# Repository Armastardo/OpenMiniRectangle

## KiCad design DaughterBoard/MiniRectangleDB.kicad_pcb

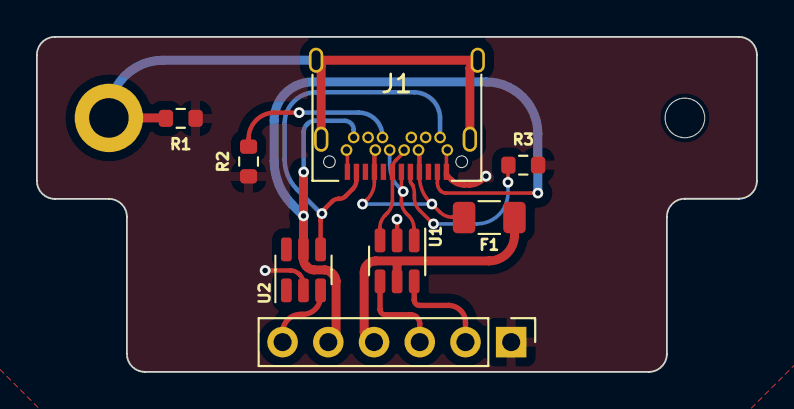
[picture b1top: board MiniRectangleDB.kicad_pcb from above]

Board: 2 copper layers, 40.0 x 18.6 mm, 10 parts (0 on the bottom side), 13 nets.

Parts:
F1: 500 mA; Fuse_1206_3216Metric
H1: MountingHole; MountingHole_2.2mm_M2
H2: MountingHole_Pad; MountingHole_2.2mm_M2_DIN965_Pad
J1: USB C Connector; TYPE-C_24P_QCHT
J2: Conn_01x06; PinHeader_1x06_P2.54mm_Vertical
R1: 1M; R_0603_1608Metric
R2, R3: 5.1k; R_0603_1608Metric
U1, U2: USBLC6-2SC6; SOT-23-6

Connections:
3vCable: J1.A2 (TX1+), J1.B2 (TX2+), J2.5, U2.5 (VBUS)
+5V: F1.2, J2.4, U1.5 (VBUS)
D+: J2.2, U1.6 (I/O1)
D-: J2.3, U1.4 (I/O2)
DATA: J2.6, U2.3 (I/O2)
DATABUS: J1.A11 (RX2+), J1.B11 (RX1+), U2.4 (I/O2)
DBUS+: J1.A6 (D+), J1.B6 (D+), U1.1 (I/O1)
DBUS-: J1.A7 (D-), J1.B7 (D-), U1.3 (I/O2)
GND: J1.A1 (GND), J1.A12 (GND), J1.B1 (GND), J1.B12 (GND), J2.1, R1.1, R2.1, R3.2, U1.2 (GND), U2.2 (GND)
unnamed: F1.1, J1.A4 (VBUS), J1.A9 (VBUS), J1.B4 (VBUS), J1.B9 (VBUS)
unnamed: J1.A5 (CC1), R3.1
unnamed: J1.B5 (CC2), R2.2
unnamed: H2.1, J1.S1 (SHIELD), R1.2

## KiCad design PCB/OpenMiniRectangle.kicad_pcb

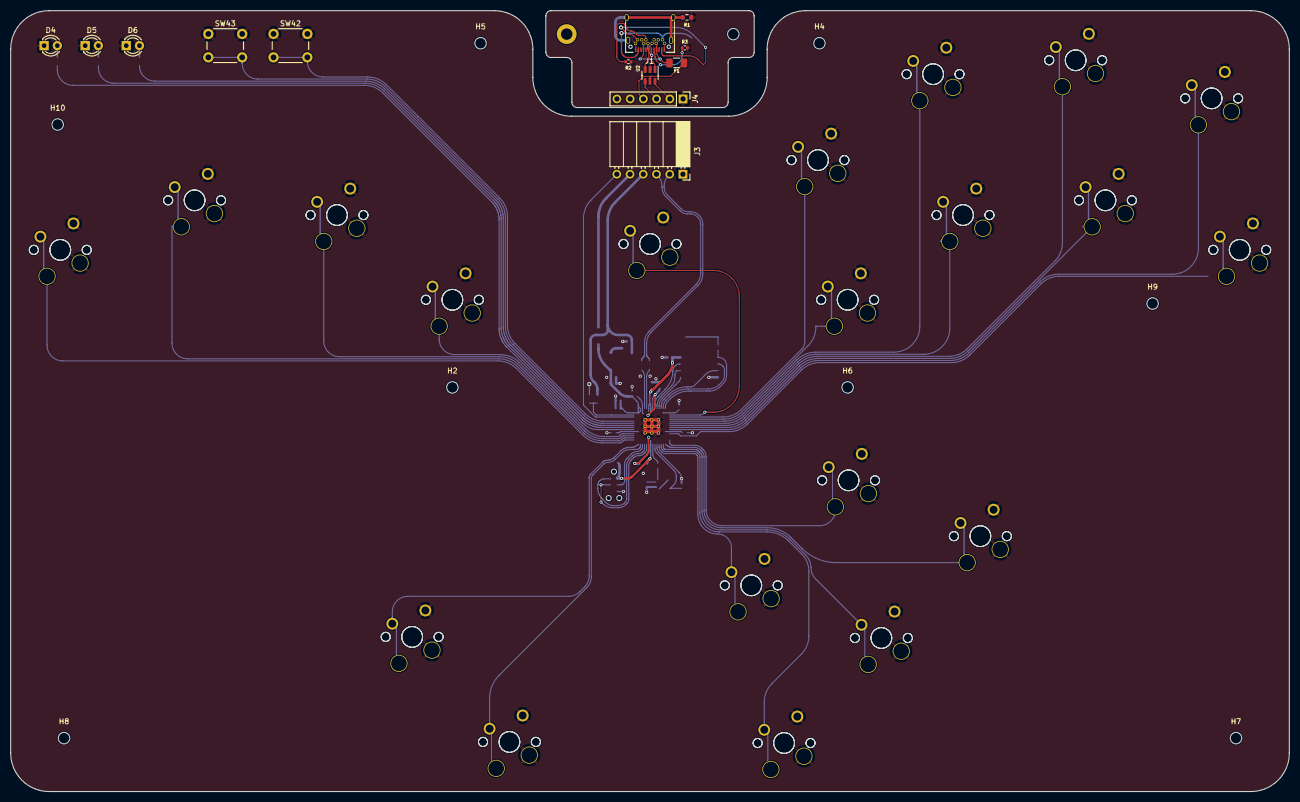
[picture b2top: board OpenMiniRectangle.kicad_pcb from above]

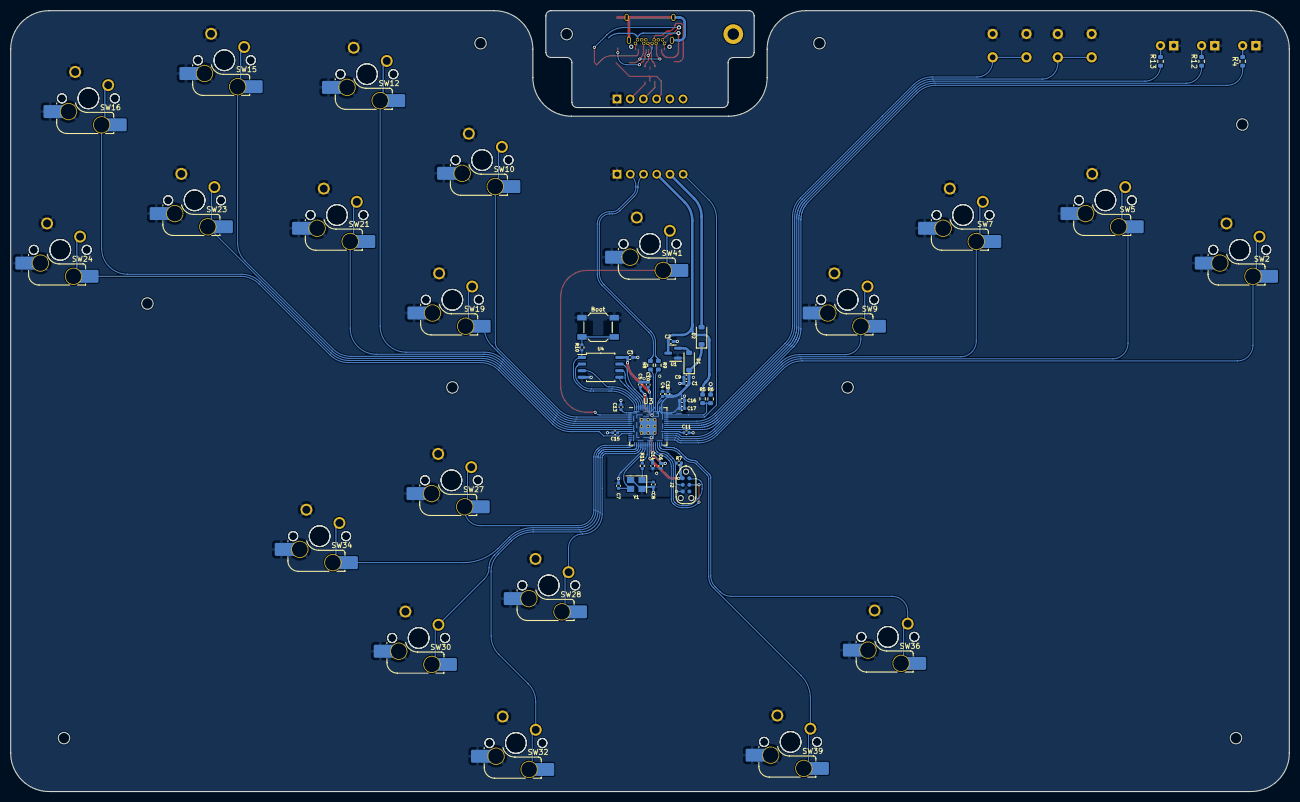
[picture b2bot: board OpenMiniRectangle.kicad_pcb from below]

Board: 2 copper layers, 245.6 x 150.0 mm, 98 parts (55 on the bottom side), 59 nets.

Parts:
C1, C2, C4, C10: 1uF; C_0402_1005Metric
C3, C5, C6, C11, C12, C13, C14, C15, C16, C17: 100nF; C_0402_1005Metric
C7, C8: 22pF; C_0402_1005Metric
C9: 10uF; C_0402_1005Metric
D1, D2: Schottky Diode; D_SOD-123
D4, D5, D6: LED; LED_D3.0mm
F1: 500 mA; Fuse_1206_3216Metric
H1, H2, H4, H5, H6, H7, H8, H9, H10: MountingHole; MountingHole_2.2mm_M2
H3: MountingHole_Pad; MountingHole_2.2mm_M2_DIN965_Pad
J1: USB C Connector; TYPE-C_24P_QCHT
J2: JTAG_TC2030; CON_TC2030_outlined
J3: Conn_01x06; PinSocket_1x06_P2.54mm_Horizontal
J4: Conn_01x06; PinHeader_1x06_P2.54mm_Vertical
R1: 1M; R_0603_1608Metric
R2, R3: 5.1k; R_0402_1005Metric
R4, R12, R13: 1k; R_0603_1608Metric
R5: 5.6k; R_0603_1608Metric
R6: 10k; R_0603_1608Metric
R7: 10k; R_0402_1005Metric
R8, R9: 27; R_0603_1608Metric
R10, R11: 1k; R_0402_1005Metric
SW1: Boot; SW_SPST_SKQG_WithStem
SW2, SW5, SW7, SW9, SW10, SW12, SW15, SW16, SW19, SW21, SW23, SW24, SW27, SW28, SW30, SW32, SW34, SW36, SW39, SW41: MX_SW_HS; SW_MX_HS_1u
SW3, SW4, SW6, SW8, SW11, SW13, SW14, SW17, SW18, SW20, SW22, SW25, SW26, SW29, SW31, SW33, SW35, SW37, SW38, SW40: MX_SW_solder; SW_MX_1u
SW42, SW43: SW_Push; SW_PUSH_6mm
U1: XC6206; SOT-23
U2: USBLC6-2SC6; SOT-23-6
U3: RP2040; RP2040-QFN-56
U4: W25Q128JVS; SOIC-8_5.23x5.23mm_P1.27mm
Y1: 12MHz; Crystal_SMD_3225-4Pin_3.2x2.5mm

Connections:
3vCable: D2.2 (A), J1.A2 (TX1+), J1.B2 (TX2+), J3.5, J4.5
+1V1: C4.1, C5.1, C6.1, U3.23 (DVDD), U3.45 (VREG_VOUT), U3.50 (DVDD)
+3V3: C1.2, C3.1, C9.1, C10.1, C11.1, C12.1, C13.1, C14.1, C15.1, C16.1, C17.1, D1.1 (K), D2.1 (K), J2.1 (VCC), R7.1, U3.1 (IOVDD), U3.10 (IOVDD), U3.22 (IOVDD), U3.33 (IOVDD), U3.42 (IOVDD), U3.43 (ADC_AVDD), U3.44 (VREG_VIN), U3.48 (USB_VDD), U3.49 (IOVDD), U4.8 (VCC)
+5V: C2.2, F1.2, J3.4, J4.4, R5.1, U1.3 (VI), U2.5 (VBUS)
/D_+: R8.2, U3.47 (D+)
/D_-: R9.2, U3.46 (D-)
/XTAL_O: C8.2, R11.1, Y1.1
/~USB_BOOT: R10.1, SW1.2
A: SW30.2, SW31.1, U3.16 (GPIO13)
B: SW18.1, SW19.2, U3.4 (GPIO2)
CS: R10.2, U3.56 (QSPI_SS_N), U4.1 (~CS)
C_DN: SW32.2, SW33.1, U3.17 (GPIO14)
C_LT: SW28.2, SW29.1, U3.18 (GPIO15)
C_RT: SW34.2, SW35.1, U3.15 (GPIO12)
C_UP: SW26.1, SW27.2, U3.14 (GPIO11)
D+: J3.2, J4.2, R8.1, U2.6 (I/O1)
D-: J3.3, J4.3, R9.1, U2.4 (I/O2)
DATA: J1.A11 (RX2+), J1.B11 (RX1+), J3.6, J4.6, U3.40 (GPIO28/ADC2)
DBUS+: J1.A6 (D+), J1.B6 (D+), U2.1 (I/O1)
DBUS-: J1.A7 (D-), J1.B7 (D-), U2.3 (I/O2)
DOWN: SW6.1, SW7.2, U3.31 (GPIO20)
GND: C1.1, C2.1, C3.2, C4.2, C5.2, C6.2, C7.1, C8.1, C9.2, C10.2, C11.2, C12.2, C13.2, C14.2, C15.2, C16.2, C17.2, D4.1 (K), D5.1 (K), D6.1 (K), J1.A1 (GND), J1.A12 (GND), J1.B1 (GND), J1.B12 (GND), J2.5 (GND), J3.1, J4.1, R1.1, R2.1, R3.2, R6.2, SW1.1, SW2.1, SW3.2, SW4.2, SW5.1, SW6.2, SW7.1, SW8.2, SW9.1, SW10.1, SW11.2, SW12.1, SW13.2, SW14.2, SW15.1, SW16.1, SW17.2, SW18.2, SW19.1, SW20.2, SW21.1, SW22.2, SW23.1, SW24.1, SW25.2, SW26.2, SW27.1, SW28.1, SW29.2, SW30.1, SW31.2, SW32.1, SW33.2, SW34.1, SW35.2, SW36.1, SW37.2, SW38.2, SW39.1, SW40.2, SW41.1, SW42.1, SW43.1, U1.1 (GND), U2.2 (GND), U3.19 (TESTEN), U3.57 (GND), U4.4 (GND), Y1.2, Y1.4
HOME: SW42.2, U3.38 (GPIO26/ADC0)
L: SW2.2, SW3.1, U3.29 (GPIO18)
LED1: R13.1, U3.36 (GPIO24)
LED2: R12.1, U3.35 (GPIO23)
LED3: R4.1, U3.34 (GPIO22)
LEFT: SW4.1, SW5.2, U3.30 (GPIO19)
LS: SW16.2, SW17.1, U3.9 (GPIO7)
M1: SW36.2, SW37.1, U3.28 (GPIO17)
M2: SW38.1, SW39.2, U3.27 (GPIO16)
MS: SW14.1, SW15.2, U3.7 (GPIO5)
unnamed: D1.2 (A), U1.2 (VO)
unnamed: D4.2 (A), R4.2
unnamed: D5.2 (A), R12.2
unnamed: D6.2 (A), R13.2
unnamed: F1.1, J1.A4 (VBUS), J1.A9 (VBUS), J1.B4 (VBUS), J1.B9 (VBUS)
unnamed: J1.A5 (CC1), R3.1
unnamed: J1.B5 (CC2), R2.2
unnamed: J1.S1 (SHIELD), R1.2
QSPI_CLK: U3.52 (QSPI_SCLK), U4.6 (CLK)
R: SW10.2, SW11.1, U3.3 (GPIO1)
RIGHT: SW8.1, SW9.2, U3.32 (GPIO21)
SD0: U3.53 (QSPI_SD0), U4.5 (DI(IO0))
SD1: U3.55 (QSPI_SD1), U4.2 (DO(IO1))
SD2: U3.54 (QSPI_SD2), U4.3 (IO2)
SD3: U3.51 (QSPI_SD3), U4.7 (IO3)
SELECT: SW43.2, U3.37 (GPIO25)
START: SW40.1, SW41.2, U3.2 (GPIO0)
SWCLK: J2.4 (SWCLK), U3.24 (SWCLK)
SWD: J2.2 (SWDIO), U3.25 (SWDIO)
UP: SW24.2, SW25.1, U3.11 (GPIO8)
VBUS_SENSE: R5.2, R6.1, U3.41 (GPIO29/ADC3)
X: SW20.1, SW21.2, U3.6 (GPIO4)
XTAL_IN: C7.2, U3.20 (XTAL_IN), Y1.3
XTAL_OUT: R11.2, U3.21 (XTAL_OUT)
Y: SW12.2, SW13.1, U3.5 (GPIO3)
Z: SW22.1, SW23.2, U3.8 (GPIO6)
~RESET: J2.3 (~RST), R7.2, U3.26 (~RUN)

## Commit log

2023-03-23 Most things on the main PCB connected
2023-03-24 Added separated board for the DB
2023-03-24 Finished main PCB
2023-07-12 Adjusted files
2023-07-12 Adjusted .gitignore
